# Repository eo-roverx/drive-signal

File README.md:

# Drive Signal Breakout PCB Designs

Breaks out the drive signals from the STM32 to the motor drivers and encoders. Also includes headers for an IMU and the main SBC. It has the following features:

*   Connectors for 4 motors and encoders
*   LEDs for each motor (based on PWM)
*   Accepts 5V power on either USB or JST
*   Optional pull-up resistors for I2C

## Components

*   1x STM32F411CEU6 Microcontroller
*   4x 3-pin JST connectors for motor drivers
*   4x 4-pin JST connectors for motor encoders
*   1x 4-pin JST connector for IMU (I2C and 5V power) + direct female header
*   1x 3-pin JST connector for SBC (I2C)
*   1x 2-pin JST connector for 5V power
*   4x 4.7k 0805 SMD resistors (optional pull-ups for I2C)
*   4x 0805 SMD LEDs (optional motor status indicators)
*   4x 0805 SMD 2k resistors (current limiting for LEDs)
*   1x 0805 capacitor (optional for STM32 power filtering)
*   2x 3-pin JST connectors for additional I2C

## STM32 Pinouts

[STM32F411 Reference Page](https://stm32-base.org/boards/STM32F411CEU6-WeAct-Black-Pill-V2.0)

### Motor Driver

| STM32 Pin | Motor (Old Name) | MD30 Pin |
| --- | --- | --- |
| B4 | M1 (LF) | PWM |
| B5 | M1 (LF) | DIR |
| B8 | M2 (LB) | PWM |
| B9 | M2 (LB) | DIR |
| A5 | M3 (RB) | PWM |
| A6 | M3 (RB) | DIR |
| A1 | M4 (RF) | PWM |
| A2 | M4 (RF) | DIR |

### Motor Encoder

| STM32 Pin | Motor (Old Name) | Encoder Pin |
| --- | --- | --- |
| B12 | M1 (LF) | B |
| B13 | M1 (LF) | A |
| B14 | M2 (LB) | B |
| B15 | M2 (LB) | A |
| A3 | M3 (RB) | B |
| A4 | M3 (RB) | A |
| C14 | M4 (RF) | B |
| C15 | M4 (RF) | A |

### I2C

| STM32 Pin | Device | I2C Pin |
| --- | --- | --- |
| B6 | IMU | SCL (1) |
| B7 | IMU | SDA (1) |
| B10 | Jetson | SCL (2) |
| B3 | Jetson | SDA (2) |

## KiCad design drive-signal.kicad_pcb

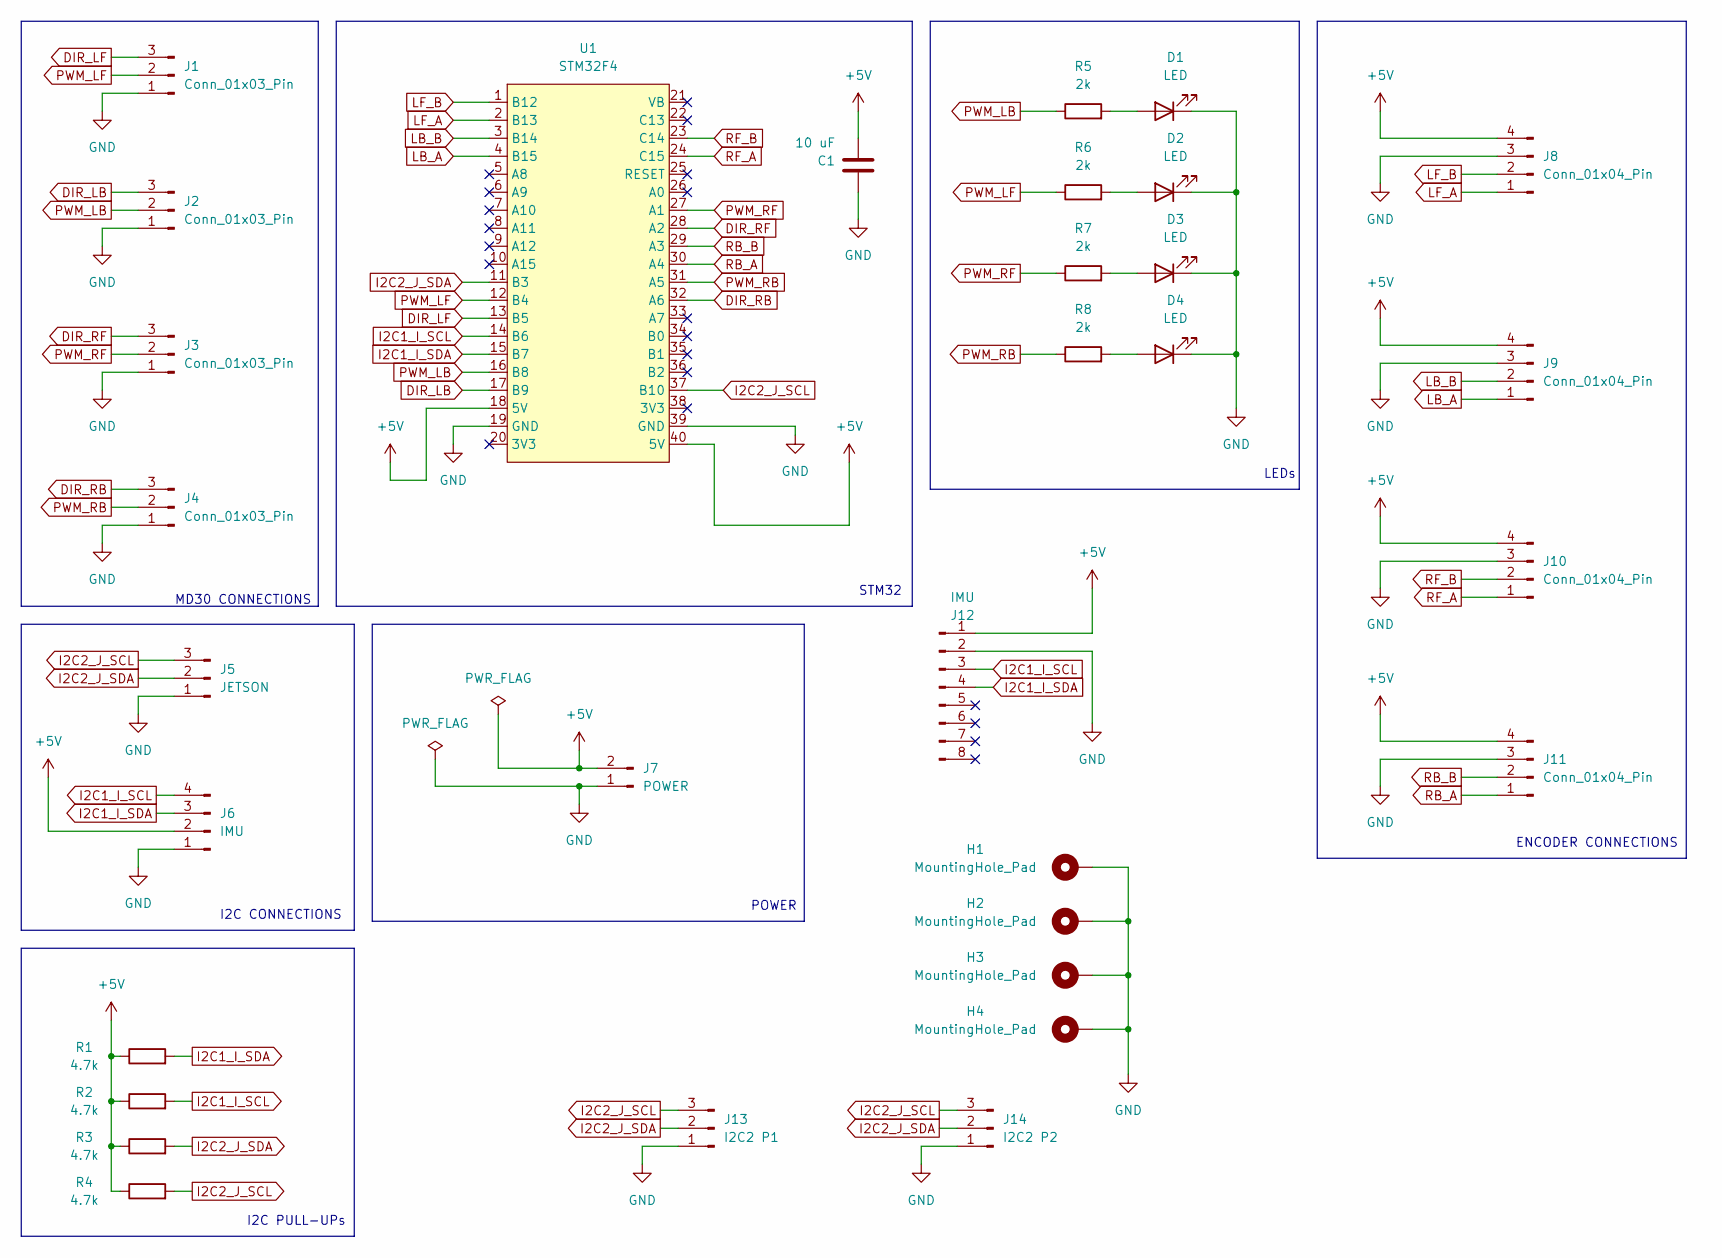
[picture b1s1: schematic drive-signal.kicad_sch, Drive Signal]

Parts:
C1: 10 uF; C_0805_2012Metric_Pad1.18x1.45mm_HandSolder
D1, D2, D3, D4: LED; LED_0805_2012Metric_Pad1.15x1.40mm_HandSolder
H1, H2, H3, H4: MountingHole_Pad; MountingHole_3.2mm_M3_Pad_Via
J1, J2, J3, J4: Conn_01x03_Pin; JST_EH_S3B-EH_1x03_P2.50mm_Horizontal
J5: JETSON; JST_EH_B3B-EH-A_1x03_P2.50mm_Vertical
J6: IMU; JST_EH_B4B-EH-A_1x04_P2.50mm_Vertical
J7: POWER; JST_EH_B2B-EH-A_1x02_P2.50mm_Vertical
J8, J9, J10, J11: Conn_01x04_Pin; JST_EH_S4B-EH_1x04_P2.50mm_Horizontal
J12: IMU; PinHeader_1x08_P2.54mm_Vertical
J13: I2C2 P1; JST_EH_S3B-EH_1x03_P2.50mm_Horizontal
J14: I2C2 P2; JST_EH_S3B-EH_1x03_P2.50mm_Horizontal
R1, R2, R3, R4: 4.7k; R_0805_2012Metric_Pad1.20x1.40mm_HandSolder
R5, R6, R7, R8: 2k; R_0805_2012Metric_Pad1.20x1.40mm_HandSolder
U1: STM32F4; STM32-BREAKOUT

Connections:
+5V: C1.1, J6.2, J7.2, J8.4, J9.4, J10.4, J11.4, J12.1, R1.1, R2.1, R3.1, R4.1, U1.18 (5V), U1.40 (5V)
DIR_LB: J2.3, U1.17 (B9)
DIR_LF: J1.3, U1.13 (B5)
DIR_RB: J4.3, U1.32 (A6)
DIR_RF: J3.3, U1.28 (A2)
GND: C1.2, D1.1 (K), D2.1 (K), D3.1 (K), D4.1 (K), H1.1, H2.1, H3.1, H4.1, J1.1, J2.1, J3.1, J4.1, J5.1, J6.1, J7.1, J8.3, J9.3, J10.3, J11.3, J12.2, J13.1, J14.1, U1.19 (GND), U1.39 (GND)
I2C1_I_SCL: J6.4, J12.3, R2.2, U1.14 (B6)
I2C1_I_SDA: J6.3, J12.4, R1.2, U1.15 (B7)
I2C2_J_SCL: J5.3, J13.3, J14.3, R4.2, U1.37 (B10)
I2C2_J_SDA: J5.2, J13.2, J14.2, R3.2, U1.11 (B3)
LB_A: J9.1, U1.4 (B15)
LB_B: J9.2, U1.3 (B14)
LF_A: J8.1, U1.2 (B13)
LF_B: J8.2, U1.1 (B12)
unnamed: D1.2 (A), R5.2
unnamed: D2.2 (A), R6.2
unnamed: D3.2 (A), R7.2
unnamed: D4.2 (A), R8.2
PWM_LB: J2.2, R5.1, U1.16 (B8)
PWM_LF: J1.2, R6.1, U1.12 (B4)
PWM_RB: J4.2, R8.1, U1.31 (A5)
PWM_RF: J3.2, R7.1, U1.27 (A1)
RB_A: J11.1, U1.30 (A4)
RB_B: J11.2, U1.29 (A3)
RF_A: J10.1, U1.24 (C15)
RF_B: J10.2, U1.23 (C14)

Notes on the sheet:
STM32
LEDs
MD30 CONNECTIONS
I2C PULL-UPs
POWER
I2C CONNECTIONS
ENCODER CONNECTIONS

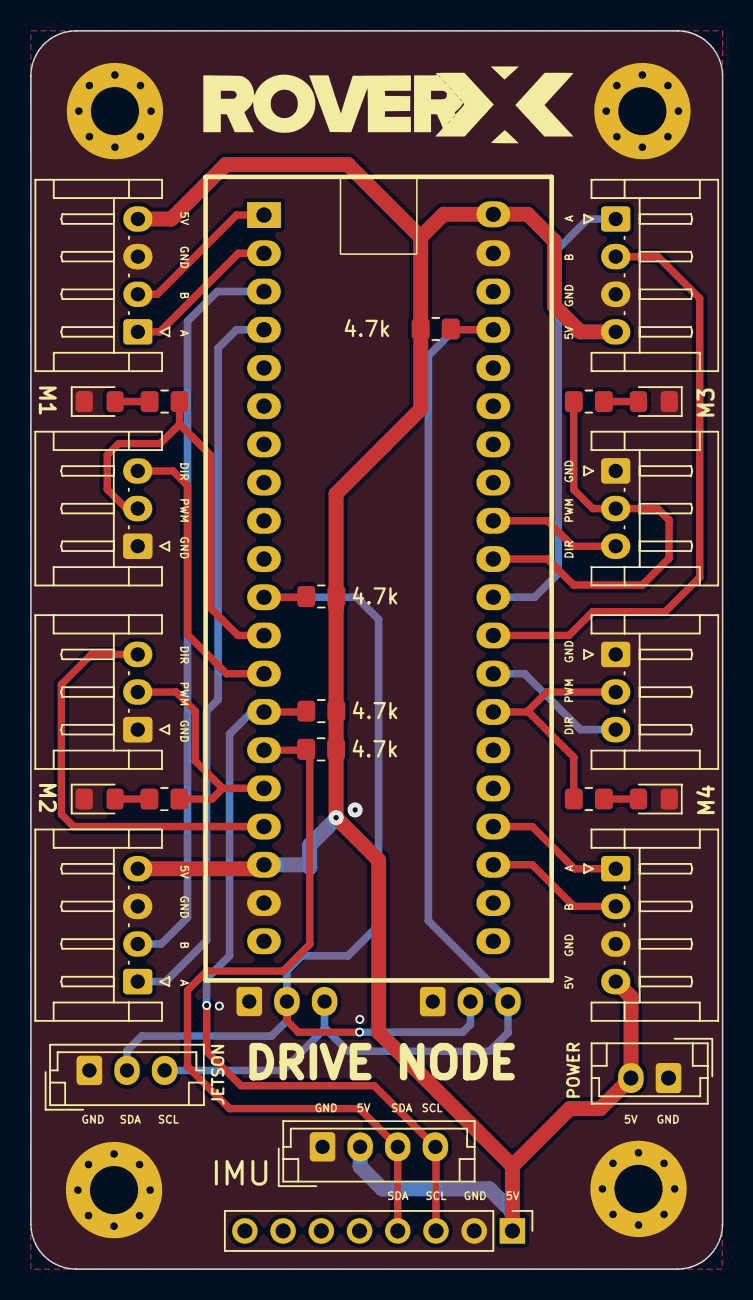
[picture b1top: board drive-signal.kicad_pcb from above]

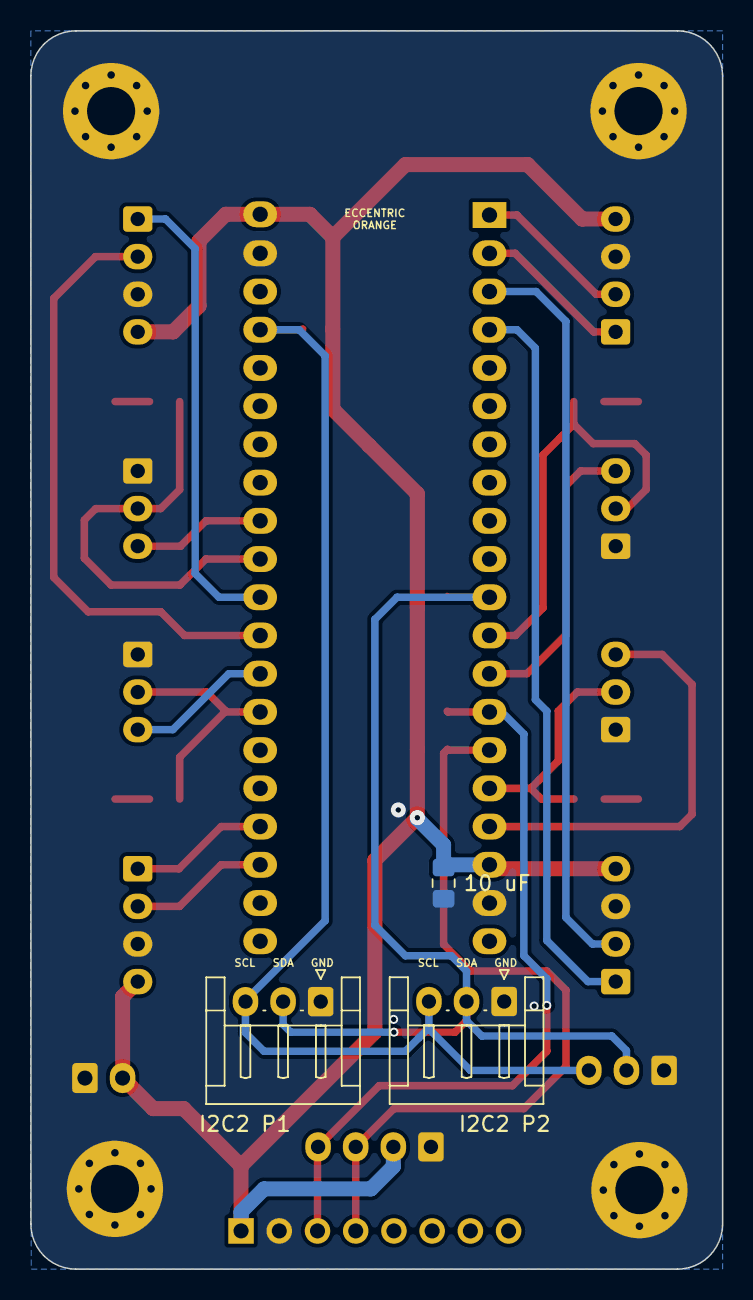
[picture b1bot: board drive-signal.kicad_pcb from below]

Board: 2 copper layers, 46.0 x 82.3 mm, 32 parts (3 on the bottom side), 26 nets.

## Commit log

2023-12-05 lay out basic PCB
2023-12-05 finish one iteration
2023-12-05 fix MD30 pinout
2023-12-05 incorporate feedback
2023-12-07 add gerbers
2023-12-08 fix mount holes
2023-12-10 add readme
2023-12-26 make JSTs horizontal
2023-12-26 minor layout improvements
2023-12-26 add mounting holes with pads
2023-12-26 change physical dims to use via-ed holes
2023-12-26 reduce mounting holes
2024-01-09 done placement
2024-01-09 done something
2024-01-10 vias and cleanup
2024-01-10 done
